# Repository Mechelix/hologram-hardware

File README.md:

# Hologram Dash and Dash Pro Hardware Repo

Welcome to Hologram
We hope you enjoy using our hardware

This is the repo for the Dash and Dash Pro

You can find everything you need to at
https://hologram.io/start

You can find the user manual here:
https://hologram.io/docs/hardware/hologram-dash/

There is also a great index of documentation here:
https://hologram.io/docs/

You can find our forums here. We really want to hear about your projects!
https://community.hologram.io/

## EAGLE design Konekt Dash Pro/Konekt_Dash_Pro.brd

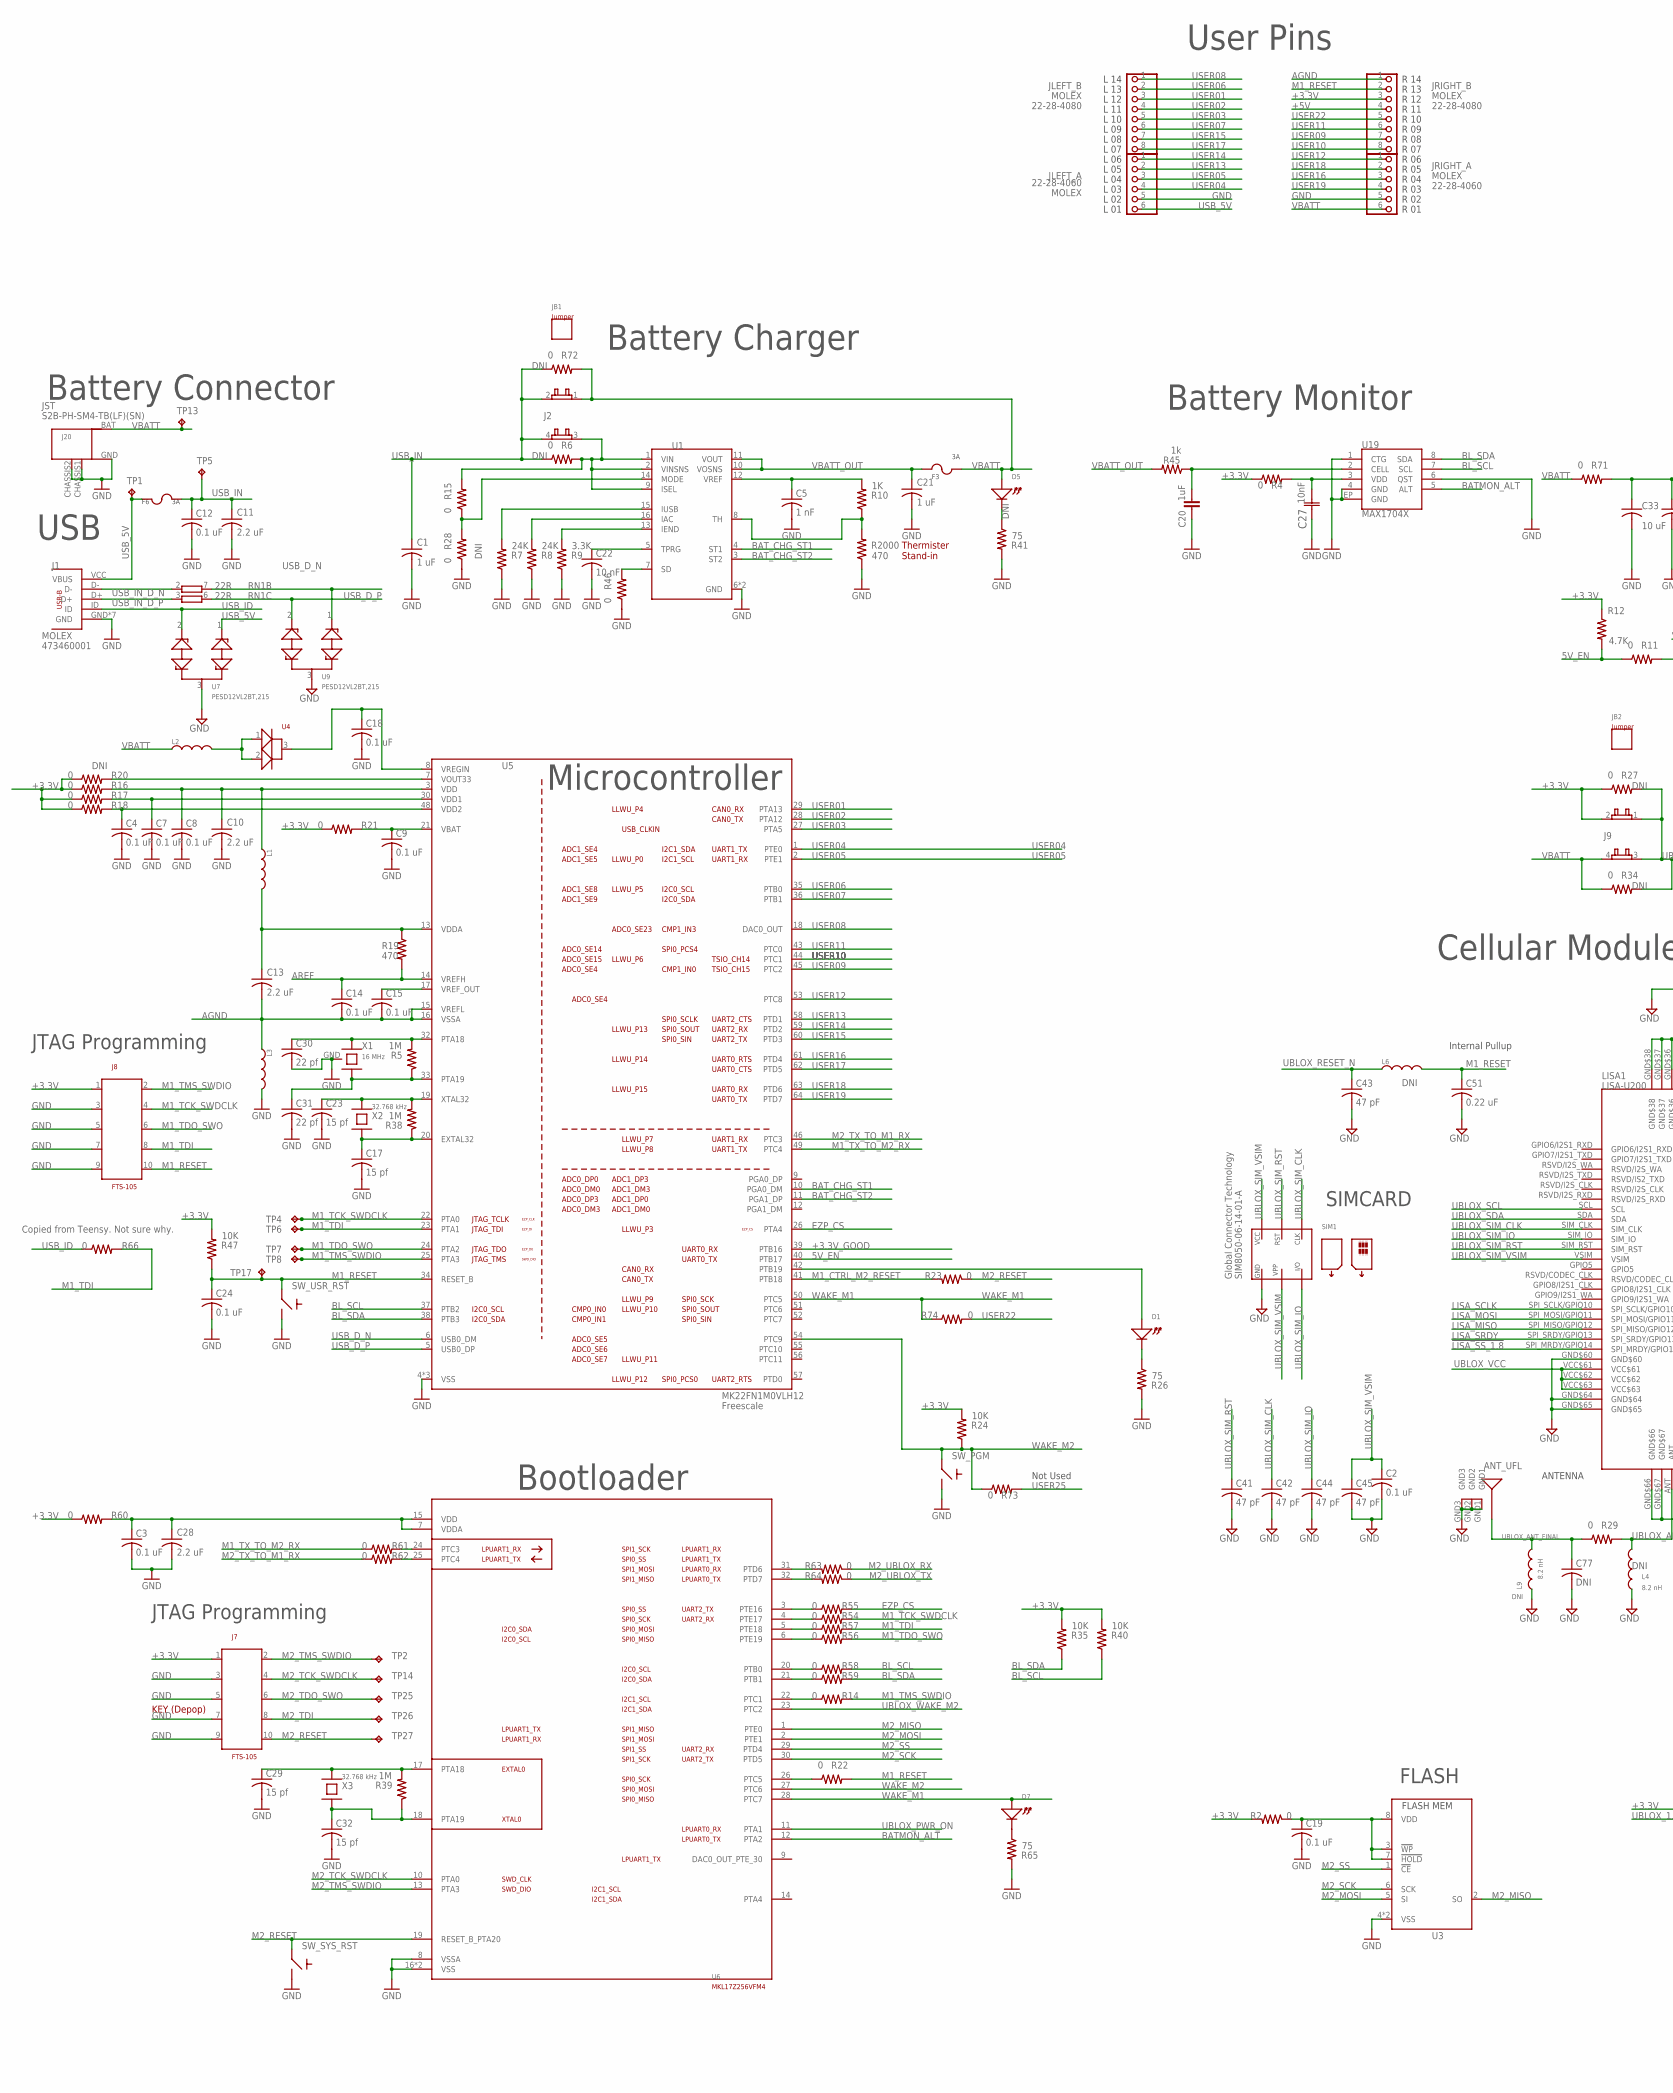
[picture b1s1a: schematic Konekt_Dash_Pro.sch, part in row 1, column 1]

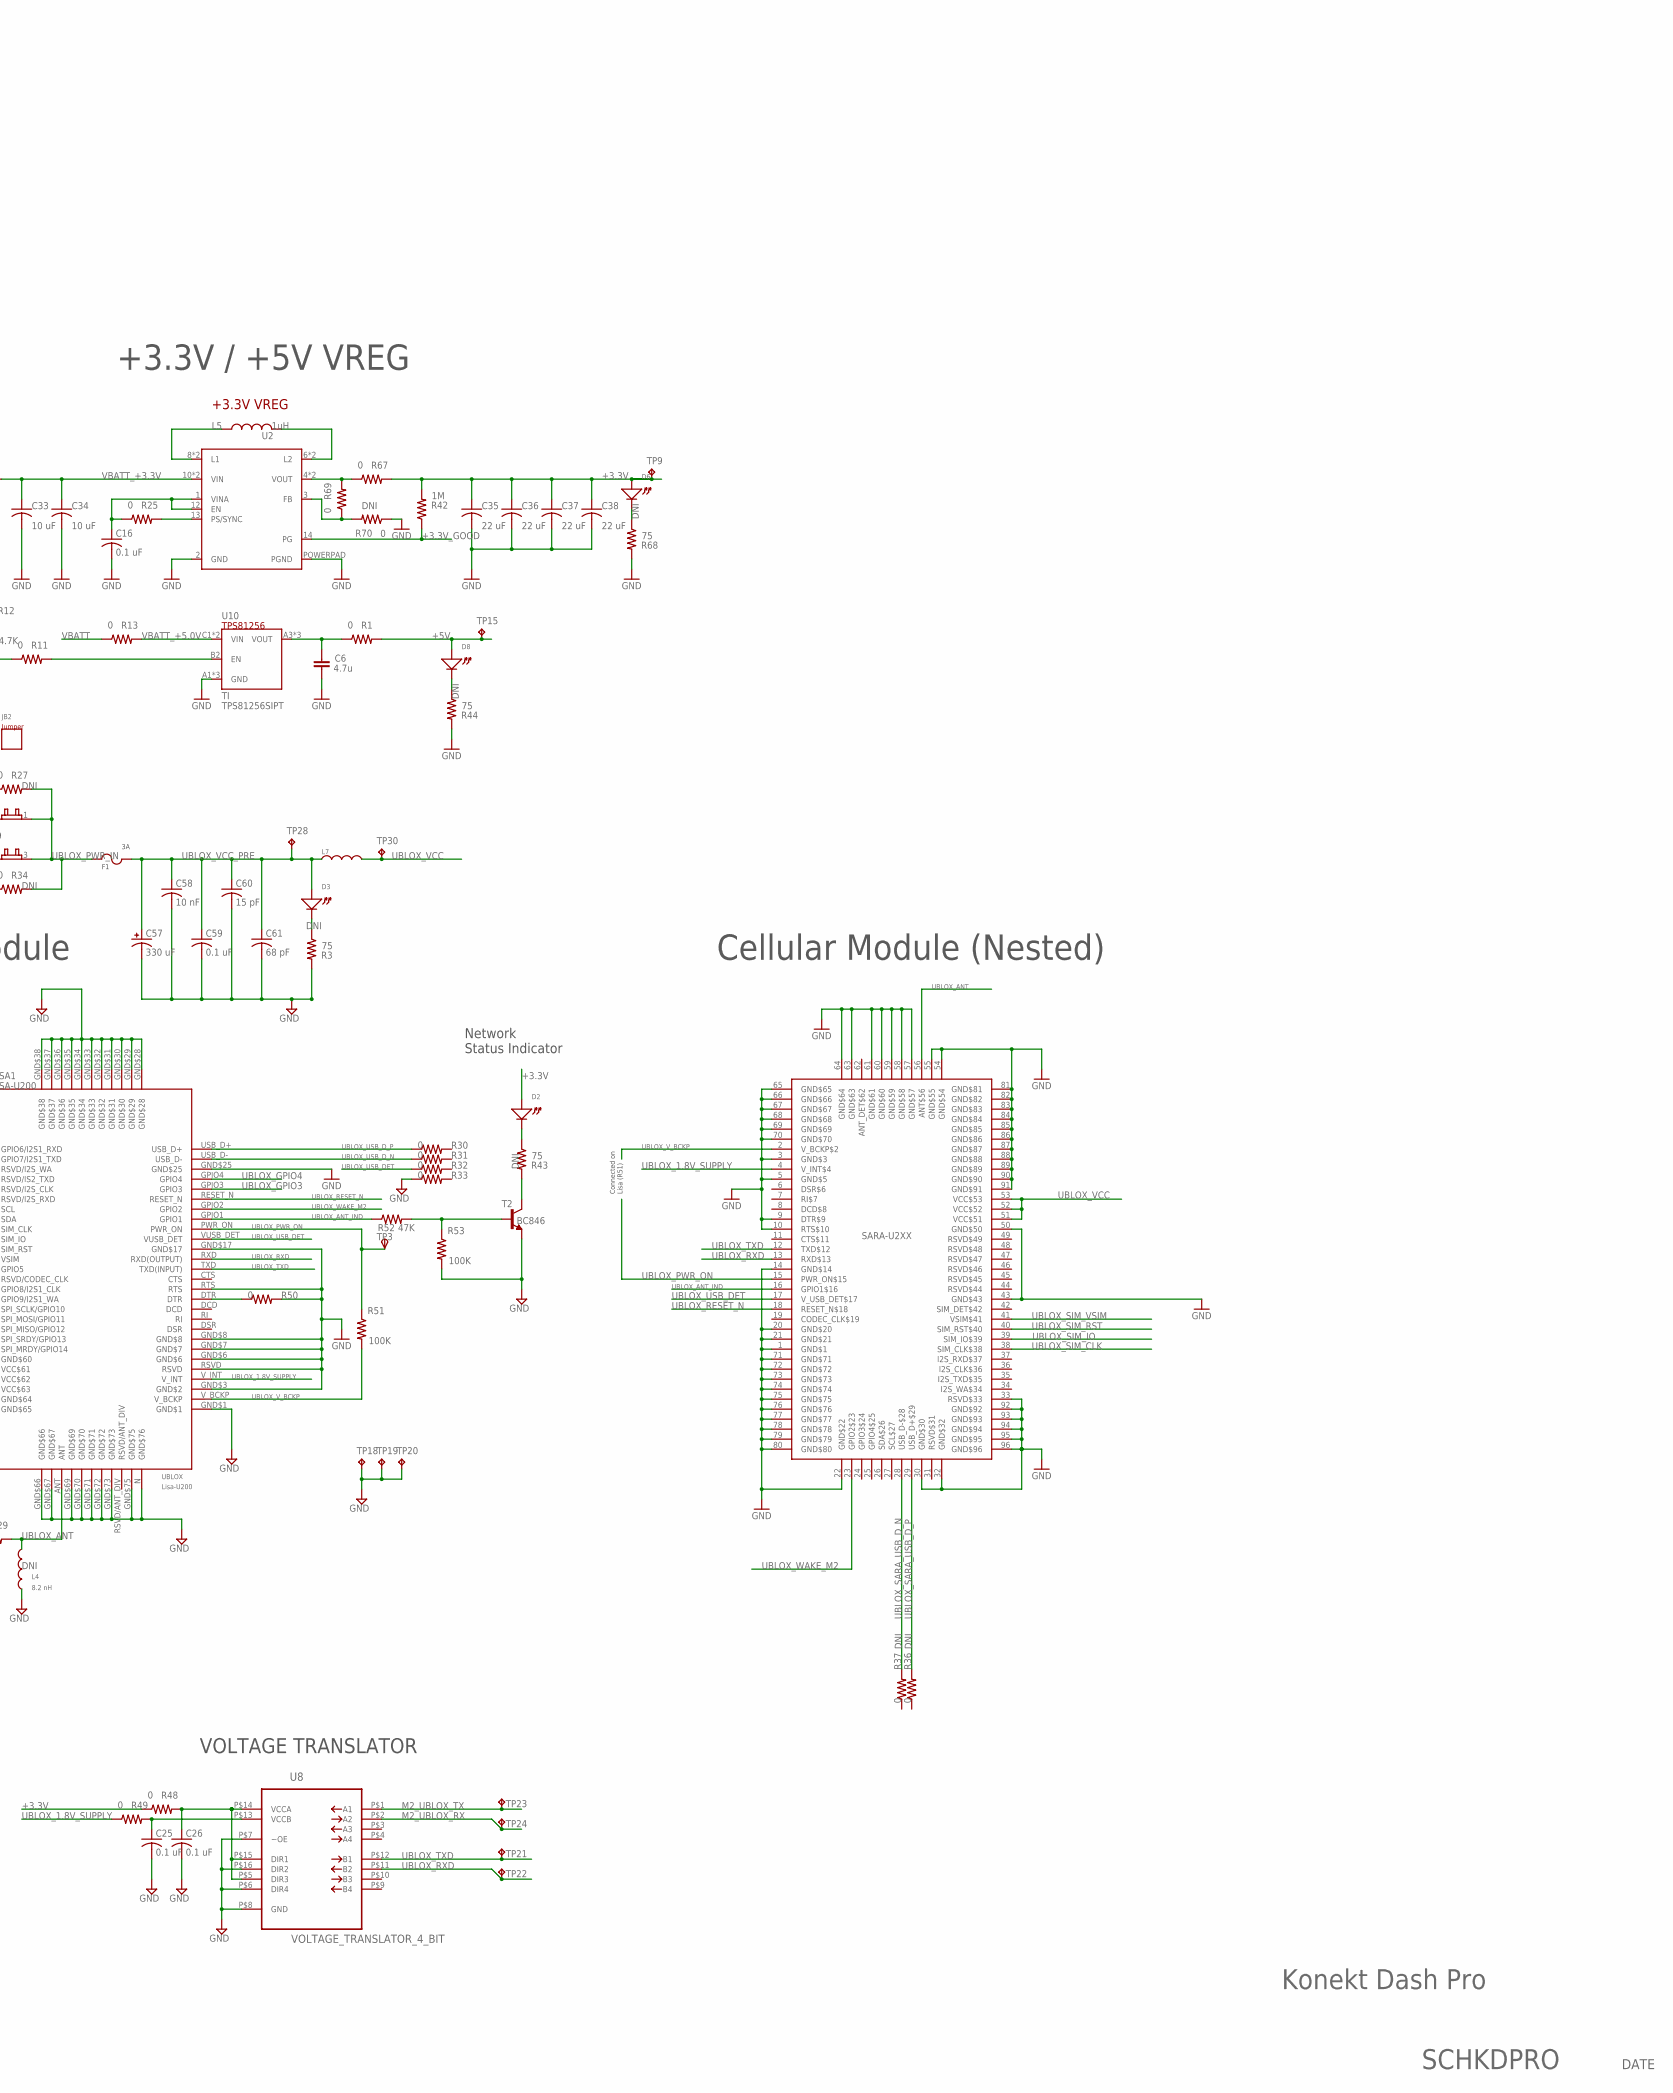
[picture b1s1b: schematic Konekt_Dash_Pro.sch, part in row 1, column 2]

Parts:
ANT_UFL: ANT-A-1JB; UFL; MPN A-1JB
C1, C21: 1 uF; C0603; MPN GRM188R71C105KA12D
C2, C3, C4, C7, C8, C9, C14, C15, C18, C19, C24, C25, C26: 0.1 uF; C0402; MPN GRM155R61C104KA88D
C5: 1 nF; C0402; MPN GRM319R71H102KA01D
C6: 4.7u; C0603-ROUND; MPN GRM188R61C475KAAJD
C10, C11, C13, C28: 2.2 uF; C0603; MPN CL10A225MQ8NNNC
C12, C16, C59: 0.1 uF; C0603; MPN 0603YC104KAT2A
C17, C23, C29, C32: 15 pf; C0402; MPN 04025A150JAT2A
C20: 1uF; 0402-CAP; TOLERANCE 10%; VOLTAGE 50V; MPN 04026D105KAT2A
C22, C58: 10 nF; C0402; MPN GRM155R71C103KA01D
C27: 10nF; CAPC1005X60N
C30, C31: 22 pf; C0402; MPN 04025A220JAT2A
C33, C34: 10 uF; C0603; MPN GRM188R60J106ME84D
C35, C36, C37, C38: 22 uF; C0603; MPN GRM188R60J226MEA0D
C41, C42, C43, C44, C45: 47 pF; C0402; MPN 04025A470JAT2A
C51: 0.22 uF; C0603; MPN 0603YC224KAT2A
C57: 330 uF; CAP_SMD_SIZE_D; MPN T520D337M006ATE045
C60: 15 pF; C0402; MPN NMC0402NPO150J50TRPF
C61: 68 pF; C0402; MPN GRM1555C1H680JA01D
C77: DNI; C0402; MPN DNI
D1, D2, D3, D5, D6, D7, D8: LED_0402_VLMW; LED_0402_VISHAY_VLMW
F1, F3, F6: 3A; R0603; MPN SF-0603S300-2
J1: USB_MICRO_B_MOLEX_473460001; USB_MICRO_MOLEX_473460001; MPN 473460001
J2, J9: CON_JUMPER_1.27_2X2; FCI_CON_1.27_2X2
J7, J8: FTS-105; MPN FTS-105-01-F-DV
J20: BAT_TERM; JST-PH-2; MPN S2B-PH-SM4-TB(LF)(SN)
JB1, JB2: JUMPER_1.27MM; NOTHING
JLEFT_A: PINHD-1X6; 1X06; MPN 22-28-4060
JLEFT_B: HEADER_0.1_IN_8_POS; HEADER_0.1_8_POS; MPN 22-28-4080
JRIGHT_A: PINHD-1X6; 1X06; MPN 22-28-4060
JRIGHT_B: HEADER_0.1_IN_8_POS; HEADER_0.1_8_POS; MPN 22-28-4080
L1, L3: INDUCTOR_0603; R0603$1; MPN BLM18AG121SN1D
L2: INDUCTOR_0603; R0603$1; MPN MPZ1608S221A
L4, L9: INDUCTOR_0402; R0402; MPN DNI
L5: 1uH; COILCRAFT_XFL4020
L6: INDUCTOR_0603; R0603$1; MPN DNI
L7: INDUCTOR_0603; R0603$1; MPN BLM18EG221SN1D
LISA1: LISA-U200; 76PIN_LCC; MPN LISA-U200-02S
R1, R2, R4, R11, R13, R14, R15, R16, R17, R18, R21, R22, R23, R25, R29, R30, R31, R32, R33, R46, R48, R49, R50, R54, R55, R56, R57, R58, R59, R60, R61, R62, R63, R64, R66, R67, R69, R71, R73, R74: 0; 0402-RES; MPN ERJ-2GE0R00X
R3, R41, R43, R44, R68: 75; 0402-RES; MPN DNI
R5, R38, R39, R42: 1M; 0402-RES; MPN RC0402JR-071ML
R6, R20, R27, R28, R34, R36, R37, R70, R72: 0; 0402-RES; MPN DNI
R7, R8: 24K; 0402-RES; MPN RC0402JR-0724KL
R9: 3.3K; 0402-RES; MPN RC0402JR-073K3L
R10: 1K; 0402-RES; MPN RC0402JR-071KL
R12: 4.7K; R0402; MPN ERJ-2GEJ472X
R19: 470; R0402; MPN ERJ-2GEJ471X
R24, R35, R40, R47: 10K; 0402-RES; MPN RC0402JR-0710KL
R26, R65: 75; 0402-RES; MPN ERJ-2GEJ750X
R45: 1k; 0402-RES; TOLERANCE 5%; MPN RC0402JR-071KL
R51, R53: 100K; R0402; MPN ERJ-2GEJ104X
R52: 47K; R0402; MPN ERJ-2GEJ473X
R2000: 470; 0402-RES; MPN RC0402JR-07470RL
RN1: 22R; CAY16; MPN CAY16-220J4LF
SARA1: SARA-U2XX; 91-PIN_LGA; MPN DNI
SIM1: SIM_CARD_NANO_GLOBAL_CONNECTOR_TEC_SIM8050-6-0-14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; SIM_CARD_NANO
SW_PGM: SWITCH_PANASONIC_EVP-BB2A1B000; SWITCH_PANASONIC_EVPBB
SW_SYS_RST: SWITCH_PANASONIC_EVP-BB2A1B000; SWITCH_PANASONIC_EVPBB
SW_USR_RST: SWITCH_PANASONIC_EVP-BB2A1B000; SWITCH_PANASONIC_EVPBB
T2: BC846; SOT23; MPN BC846ALT1G
TP1, TP2, TP4, TP5, TP6, TP7, TP8, TP9, TP13, TP14, TP15, TP17, TP18, TP19, TP20, TP21, TP22, TP23, TP24, TP25, TP26, TP27, TP28, TP30: TPTP08R; TP08R; MPN N/A
TP3: TPSTP09R; TP09R; MPN N/A
U1: ST_MICRO_BAT_CHARGER_L6924U013; BAT_CHARGE_ST_MICRO_L6924U; MPN L6924UTR
U2: TPS63021; QFN-14-POWERPAD3X4DSJ; MPN TPS63021DSJR
U3: MICROCHIP_FLASH_MEM; TDFN8_5X6; MPN SST26VF016BT-104I/MF
U4: DIODE_DUAL_SCHOTKEY; SOT23-3; MPN_DNI BAT54C
U5: MK20DX128VLH5; MPN MK22FN1M0VLH12
U6: FREESCALE_MKL17Z256VFM4; QFN_32_5X5
U7, U9: PESD12VL2BT,215; SOT23; MPN PESD12VL2BT,215
U8: VOLTAGE_TRANSLATOR_4_BIT; UQFN_16
U10: BOOST_5V_TI_TPS81256; MICRO_SIP_3X3
U19: MAX1704X; TDFN-8; MPN MAX17043G+U
X1: 16 MHz; CRYSTAL_RESONATOR_MURATA_CSTCE
X2, X3: 32.768 kHz; CRYSTAL_ST3215SB

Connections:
5V_EN: R11.1, R12.2, U5.40 (PTB17)
!LISA_SS_1.8: LISA1.SPI_MRDY/GPIO14
+3.3V: C35.1, C36.1, C37.1, C38.1, D2.ANODE, D6.ANODE, J7.1, J8.1, J9.2, JRIGHT_B.3, R2.2, R4.1, R12.1, R16.1, R17.1, R18.1, R20.1, R21.1, R24.2, R27.1, R35.2, R40.2, R42.2, R47.2, R48.1, R60.1, R67.2, TP9.TP
+3.3V_FLASH: C19.1, R2.1, U3.3 (!WP), U3.7 (!HOLD), U3.8 (VDD)
+3.3V_GOOD: R42.1, U2.14 (PG), U5.39 (PTB16)
+5V: D8.ANODE, JRIGHT_B.4, R1.2, TP15.TP
AGND: C13.2, C14.2, C15.2, JRIGHT_B.1, L3.1, U5.15 (VREFL), U5.16 (VSSA)
ANT_DET$62: SARA1.62 (ANT_DET$62)
AREF: C14.1, R19.2, U5.14 (VREFH)
BATMON_ALT: U6.12 (PTA2), U19.5 (ALT)
BAT_CHG_ST1: U1.4 (ST1), U5.10 (PGA0_DM)
BAT_CHG_ST2: U1.3 (ST2), U5.11 (PGA1_DP)
BL_SCL: R40.1, R58.2, U5.37 (PTB2), U19.7 (SCL)
BL_SDA: R35.1, R59.2, U5.38 (PTB3), U19.8 (SDA)
EZP_CS: R55.2, U5.26 (PTA4)
GND: ANT_UFL.GND1, ANT_UFL.GND2, ANT_UFL.GND3, C1.2, C2.2, C3.2, C4.2, C5.2, C6.1, C7.2, C8.2, C9.2, C10.2, C11.2, C12.2, C16.2, C17.2, C18.2, C19.2, C20.2, C21.2, C22.2, C23.2, C24.2, C25.2, C26.2, C27.1 (C1), C28.2, C29.2, C30.2, C31.2, C32.2, C33.2, C34.2, C35.2, C36.2, C37.2, C38.2, C41.2, C42.2, C43.2, C44.2, C45.2, C51.2, C57.P$2 (NEG), C58.2, C59.2, C60.2, C61.2, C77.2, J1.GND, J1.GND$1 (GND), J1.GND$2 (GND), J1.GND$3 (GND), J1.GND$4 (GND), J1.GND$5 (GND), J1.GND$6 (GND), J7.3, J7.5, J7.7, J7.9, J8.3, J8.5, J8.7, J8.9, J20.CHASSIS1 (CHASSIS_1), J20.CHASSIS2 (CHASSIS_2), J20.GND, JLEFT_A.5, JRIGHT_A.5, L3.2, L4.2, L9.2, LISA1.GND$1, LISA1.GND$3 (GND$2), LISA1.GND$6, LISA1.GND$7, LISA1.GND$8, LISA1.GND$17, LISA1.GND$25, LISA1.GND$28, LISA1.GND$29, LISA1.GND$30, LISA1.GND$31, LISA1.GND$32, LISA1.GND$33, LISA1.GND$34, LISA1.GND$35, LISA1.GND$36, LISA1.GND$37, LISA1.GND$38, LISA1.GND$60, LISA1.GND$64, LISA1.GND$65, LISA1.GND$66, LISA1.GND$67, LISA1.GND$69, LISA1.GND$70, LISA1.GND$71, LISA1.GND$72, LISA1.GND$73, LISA1.GND$75, LISA1.N (GND$76), LISA1.RSVD, LISA1.RTS, R3.2, R7.1, R8.1, R9.1, R26.2, R28.1, R33.1, R41.2, R44.2, R46.1, R50.2, R53.2, R65.2, R68.2, R70.1, R2000.1, SARA1.1 (GND$1), SARA1.3 (GND$3), SARA1.5 (GND$5), SARA1.9 (DTR$9), SARA1.10 (RTS$10), SARA1.14 (GND$14), SARA1.20 (GND$20), SARA1.21 (GND$21), SARA1.22 (GND$22), SARA1.30 (GND$30), SARA1.32 (GND$32), SARA1.33 (RSVD$33), SARA1.43 (GND$43), SARA1.50 (GND$50), SARA1.54 (GND$54), SARA1.55 (GND$55), SARA1.57 (GND$57), SARA1.58 (GND$58), SARA1.59 (GND$59), SARA1.60 (GND$60), SARA1.61 (GND$61), SARA1.63 (GND$63), SARA1.64 (GND$64), SARA1.65 (GND$65), SARA1.66 (GND$66), SARA1.67 (GND$67), SARA1.68 (GND$68), SARA1.69 (GND$69), SARA1.70 (GND$70), SARA1.71 (GND$71), SARA1.72 (GND$72), SARA1.73 (GND$73), SARA1.74 (GND$74), SARA1.75 (GND$75), SARA1.76 (GND$76), SARA1.77 (GND$77), SARA1.78 (GND$78), SARA1.79 (GND$79), SARA1.80 (GND$80), SARA1.81 (GND$81), SARA1.82 (GND$82), SARA1.83 (GND$83), SARA1.84 (GND$84), SARA1.85 (GND$85), SARA1.86 (GND$86), SARA1.87 (GND$87), SARA1.88 (GND$88), SARA1.89 (GND$89), SARA1.90 (GND$90), SARA1.91 (GND$91), SARA1.92 (GND$92), SARA1.93 (GND$93), SARA1.94 (GND$94), SARA1.95 (GND$95), SARA1.96 (GND$96), SIM1.C5-GND (GND), SW_PGM.B, SW_PGM.B2, SW_SYS_RST.B, SW_SYS_RST.B2, SW_USR_RST.B, SW_USR_RST.B2, T2.2 (E), TP18.TP, TP19.TP, TP20.TP, U1.6 (GND), U1.PAD (GND), U2.2 (GND), U2.POWERPAD (PGND), U3.4 (VSS), U3.P$9 (VSS), U5.4 (VSS), U5.31 (VSS), U5.47 (VSS), U6.8 (VSSA), U6.16 (VSS), U6.PAD (VSS), U7.3, U8.P$6 (DIR4), U8.P$7 (~OE), U8.P$8 (GND), U8.P$16 (DIR2), U9.3, U10.A1 (GND), U10.A2 (GND), U10.B1 (GND), U19.1 (CTG), U19.4 (GND), U19.6 (QST), U19.EP (GND), X1.GND
GPIO4$25: SARA1.25 (GPIO4$25)
I2S_TXD$35: SARA1.35 (I2S_TXD$35)
I2S_WA$34: SARA1.34 (I2S_WA$34)
LISA_MISO: LISA1.SPI_MISO/GPIO12
LISA_MOSI: LISA1.SPI_MOSI/GPIO11
LISA_SCLK: LISA1.SPI_SCLK/GPIO10
LISA_SRDY: LISA1.SPI_SRDY/GPIO13
M1_CTRL_M2_RESET: R23.2, U5.41 (PTB18)
M1_RESET: C24.1, C51.1, J8.10, JRIGHT_B.2, L6.2, R22.2, R47.1, SW_USR_RST.A, SW_USR_RST.A2, TP17.TP, U5.34 (RESET_B)
M1_TCK_SWDCLK: J8.4, R54.2, TP4.TP, U5.22 (PTA0)
M1_TDI: J8.8, R57.2, R66.2, TP6.TP, U5.23 (PTA1)
M1_TDO_SWO: J8.6, R56.2, TP7.TP, U5.24 (PTA2)
M1_TMS_SWDIO: J8.2, R14.2, TP8.TP, U5.25 (PTA3)
M1_TX_TO_M2_RX: R61.1, U5.49 (PTC4)
M2_MISO: U3.2 (SO), U6.1 (PTE0)
M2_MOSI: U3.5 (SI), U6.2 (PTE1)
M2_RESET: J7.10, R23.1, SW_SYS_RST.A, SW_SYS_RST.A2, TP27.TP, U6.19 (RESET_B_PTA20)
M2_RX: R61.2, U6.24 (PTC3)
M2_SCK: U3.6 (SCK), U6.30 (PTD5)
M2_SPI0_MISO: R56.1, U6.6 (PTE19)
M2_SPI0_MOSI: R57.1, U6.5 (PTE18)
M2_SS: U3.1 (!CE), U6.29 (PTD4)
M2_TCK_SWDCLK: J7.4, TP14.TP, U6.10 (PTA0)
M2_TDI: J7.8, TP26.TP
M2_TDO_SWO: J7.6, TP25.TP
M2_TMS_SWDIO: J7.2, TP2.TP, U6.13 (PTA3)
M2_TX: R62.2, U6.25 (PTC4)
M2_TX_TO_M1_RX: R62.1, U5.46 (PTC3)
M2_UBLOX_RX: R63.1, TP24.TP, U8.P$2 (A2)
M2_UBLOX_TX: R64.1, TP23.TP, U8.P$1 (A1)
unnamed: C20.1, R45.1, U19.2 (CELL)
unnamed: D1.ANODE, U5.42 (PTB19)
unnamed: C27.2 (C2), R4.2, U19.3 (VDD)
unnamed: J2.3, R6.2, R15.2, U1.1 (VIN), U1.2 (VINSNS), U1.9 (ISEL)
unnamed: R10.1, R2000.2, U1.8 (TH)
unnamed: C5.1, R10.2, U1.12 (VREF)
unnamed: D3.CATHODE, R3.1
unnamed: R7.2, U1.15 (IUSB)
unnamed: L5.P$1, U2.8 (L1), U2.9 (L1)
unnamed: R8.2, U1.16 (IAC)
unnamed: C30.1, R5.2, U5.32 (PTA18), X1.XTAL1
unnamed: R9.2, U1.13 (IEND)
unnamed: D5.CATHODE, R41.1
unnamed: C22.1, U1.5 (TPRG)
unnamed: C6.2, R1.1, U10.A3 (VOUT), U10.B3 (VOUT), U10.C3 (VOUT)
unnamed: R11.2, U10.B2 (EN)
unnamed: C8.1, C10.1, L1.1, R16.2, U5.3 (VDD)
unnamed: C7.1, R17.2, U5.30 (VDD1)
unnamed: C4.1, R18.2, U5.48 (VDD2)
unnamed: C18.1, U4.3 (C), U5.8 (VREGIN)
unnamed: R20.2, U5.7 (VOUT33)
unnamed: C15.1, U5.17 (VREF_OUT)
unnamed: C13.1, L1.2, R19.1, U5.13 (VDDA)
unnamed: D8.CATHODE, R44.1
unnamed: L2.2, U4.1 (A1), U4.2 (A2)
unnamed: LISA1.DTR, R50.1
unnamed: C9.1, R21.2, U5.21 (VBAT)
unnamed: C31.1, R5.1, U5.33 (PTA19), X1.XTAL2
unnamed: C23.1, R38.2, U5.19 (XTAL32), X2.P$2 (XTAL2)
unnamed: R58.1, U6.20 (PTB0)
unnamed: C17.1, R38.1, U5.20 (EXTAL32), X2.P$1 (XTAL1)
unnamed: L5.P$2, U2.6 (L2), U2.7 (L2)
unnamed: D1.CATHODE, R26.1
unnamed: C16.1, R25.1, U2.1 (VINA), U2.12 (EN)
unnamed: R14.1, U6.22 (PTC1)
unnamed: R15.1, R28.2, U1.14 (MODE)
unnamed: R46.2, U1.7 (SD)
unnamed: R67.1, R69.2, U2.4 (VOUT), U2.5 (VOUT)
unnamed: R63.2, U6.31 (PTD6)
unnamed: R64.2, U6.32 (PTD7)
unnamed: R55.1, U6.3 (PTE16)
unnamed: R54.1, U6.4 (PTE17)
unnamed: R59.1, U6.21 (PTB1)
unnamed: R22.1, U6.26 (PTC5)
unnamed: C3.1, C28.1, R60.2, U6.7 (VDDA), U6.15 (VDD)
unnamed: D7.CATHODE, R65.1
unnamed: C32.1, R39.1, U6.18 (PTA19), X3.P$1 (XTAL1)
unnamed: C29.1, R39.2, U6.17 (PTA18), X3.P$2 (XTAL2)
unnamed: R25.2, U2.13 (PS/SYNC)
unnamed: D6.CATHODE, R68.1
unnamed: R69.1, R70.2, U2.3 (FB)
unnamed: D2.CATHODE, R43.1
unnamed: R52.2, R53.1, T2.1 (B)
unnamed: R43.2, T2.3 (C)
RSVD$31: SARA1.31 (RSVD$31)
SCL$27: SARA1.27 (SCL$27)
SDA$26: SARA1.26 (SDA$26)
UBLOX_1.8V_SUPPLY: LISA1.V_INT, R49.1, SARA1.4 (V_INT$4)
UBLOX_ANT: L4.1, LISA1.ANT, R29.2, SARA1.56 (ANT$56)
UBLOX_ANT_FINAL: ANT_UFL.SIGNAL, C77.1, L9.1, R29.1
UBLOX_ANT_IND: LISA1.GPIO1, R52.1, SARA1.16 (GPIO1$16)
UBLOX_GPIO3: LISA1.GPIO3
UBLOX_GPIO4: LISA1.GPIO4
UBLOX_PWR_IN: F1.2, J9.1, J9.3, R27.2, R34.2
UBLOX_PWR_ON: LISA1.PWR_ON, R51.1, SARA1.15 (PWR_ON$15), TP3.TP, U6.11 (PTA1)
UBLOX_RESET_N: C43.1, L6.1, LISA1.RESET_N, SARA1.18 (RESET_N$18)
UBLOX_RXD: LISA1.RXD (RXD(OUTPUT)), SARA1.13 (RXD$13), TP22.TP, U8.P$11 (B2)
UBLOX_SARA_USB_D_N: R37.2, SARA1.28 (USB_D-$28)
UBLOX_SARA_USB_D_P: R36.2, SARA1.29 (USB_D+$29)
UBLOX_SCL: LISA1.SCL
UBLOX_SDA: LISA1.SDA
UBLOX_SIM_CLK: C42.1, LISA1.SIM_CLK, SARA1.38 (SIM_CLK$38), SIM1.C3-CLK (CLK)
UBLOX_SIM_IO: C44.1, LISA1.SIM_IO, SARA1.39 (SIM_IO$39), SIM1.C7-IO (IO)
UBLOX_SIM_RST: C41.1, LISA1.SIM_RST, SARA1.40 (SIM_RST$40), SIM1.C2-RST (RST)
UBLOX_SIM_VSIM: C2.1, C45.1, LISA1.VSIM, SARA1.41 (VSIM$41), SIM1.C1-VCC (VCC), SIM1.C6-VPP (VCC2)
UBLOX_TXD: LISA1.TXD (TXD(INPUT)), SARA1.12 (TXD$12), TP21.TP, U8.P$12 (B1)
UBLOX_USB_DET: LISA1.VUSB_DET, R32.1, SARA1.17 (V_USB_DET$17)
UBLOX_USB_D_N: LISA1.USB_D-, R31.1
UBLOX_USB_D_P: LISA1.USB_D+, R30.1
UBLOX_VCC: L7.2, LISA1.VCC$61, LISA1.VCC$62, LISA1.VCC$63, SARA1.51 (VCC$51), SARA1.52 (VCC$52), SARA1.53 (VCC$53), TP30.TP
UBLOX_VCC_PRE: C57.P$1 (POS), C58.1, C59.1, C60.1, C61.1, D3.ANODE, F1.1, L7.1, TP28.TP
UBLOX_V_BCKP: LISA1.V_BCKP, R51.2, SARA1.2 (V_BCKP$2)
UBLOX_WAKE_M2: LISA1.GPIO2, SARA1.23 (GPIO2$23), U6.23 (PTC2)
USB_5V: F6.1, J1.VCC (VBUS), JLEFT_A.6, TP1.TP, U7.1
USB_D_N: RN1.7 (2), U5.6 (USB0_DM), U9.1
USB_D_P: RN1.6 (2), U5.5 (USB0_DP), U9.2
USB_ID: J1.ID, R66.1, U7.2
USB_IN: C1.1, C11.1, C12.1, F6.2, J2.2, J2.4, R6.1, R72.1, TP5.TP
USB_IN_D_N: J1.D-, RN1.2 (1)
USB_IN_D_P: J1.D+, RN1.3 (1)
USER01: JLEFT_B.3, U5.29 (PTA13)
USER02: JLEFT_B.4, U5.28 (PTA12)
USER03: JLEFT_B.5, U5.27 (PTA5)
USER04: JLEFT_A.4, U5.1 (PTE0)
USER05: JLEFT_A.3, U5.2 (PTE1)
USER06: JLEFT_B.2, U5.35 (PTB0)
USER07: JLEFT_B.6, U5.36 (PTB1)
USER08: JLEFT_B.1, U5.18 (DAC0_OUT)
USER09: JRIGHT_B.7, U5.45 (PTC2)
USER10: JRIGHT_B.8, U5.44 (PTC1)
USER11: JRIGHT_B.6, U5.43 (PTC0)
USER12: JRIGHT_A.1, U5.53 (PTC8)
USER13: JLEFT_A.2, U5.58 (PTD1)
USER14: JLEFT_A.1, U5.59 (PTD2)
USER15: JLEFT_B.7, U5.60 (PTD3)
USER16: JRIGHT_A.3, U5.61 (PTD4)
USER17: JLEFT_B.8, U5.62 (PTD5)
USER18: JRIGHT_A.2, U5.63 (PTD6)
USER19: JRIGHT_A.4, U5.64 (PTD7)
USER22: JRIGHT_B.5, R74.2
USER25: R73.2
VBATT: D5.ANODE, F3.1, J2.1, J9.4, J20.BAT, JRIGHT_A.6, L2.1, R13.1, R34.1, R71.1, R72.2, TP13.TP
VBATT_+3.3V: C33.1, C34.1, R71.2, U2.10 (VIN), U2.11 (VIN)
VBATT_+5.0V: R13.2, U10.C1 (VIN), U10.C2 (VIN)
VBATT_OUT: C21.1, F3.2, R45.2, U1.10 (VOSNS), U1.11 (VOUT)
VTL_+3.3V1: C26.1, R48.2, U8.P$5 (DIR3), U8.P$14 (VCCA), U8.P$15 (DIR1)
VTL_LISA_VCC1: C25.1, R49.2, U8.P$13 (VCCB)
WAKE_M1: D7.ANODE, R74.1, U5.50 (PTC5), U6.28 (PTC7)
WAKE_M2: R24.1, R73.1, SW_PGM.A, SW_PGM.A2, U5.54 (PTC9), U6.27 (PTC6)

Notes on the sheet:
Network Status Indicator
SIMCARD
LISA1
Microcontroller
Thermister Stand-in
User Pins
Bootloader
Battery Connector
USB
Battery Charger
Battery Monitor
+3.3V / +5V VREG
ANTENNA
VOLTAGE TRANSLATOR
+3.3V VREG
EZP_CLK
EZP_DI
EZP_D0
SWD_DIO
EZP_CS
JTAG Programming
KEY (Depop)
Copied from Teensy. Not sure why.
Cellular Module (Nested)
Konekt Dash Pro
DATE
SCHKDPRO
Cellular Module
FLASH
Connected on Lisa (R51)
R 01
R 02
R 03
R 04
R 05
R 06
R 07
R 08
R 09
R 10

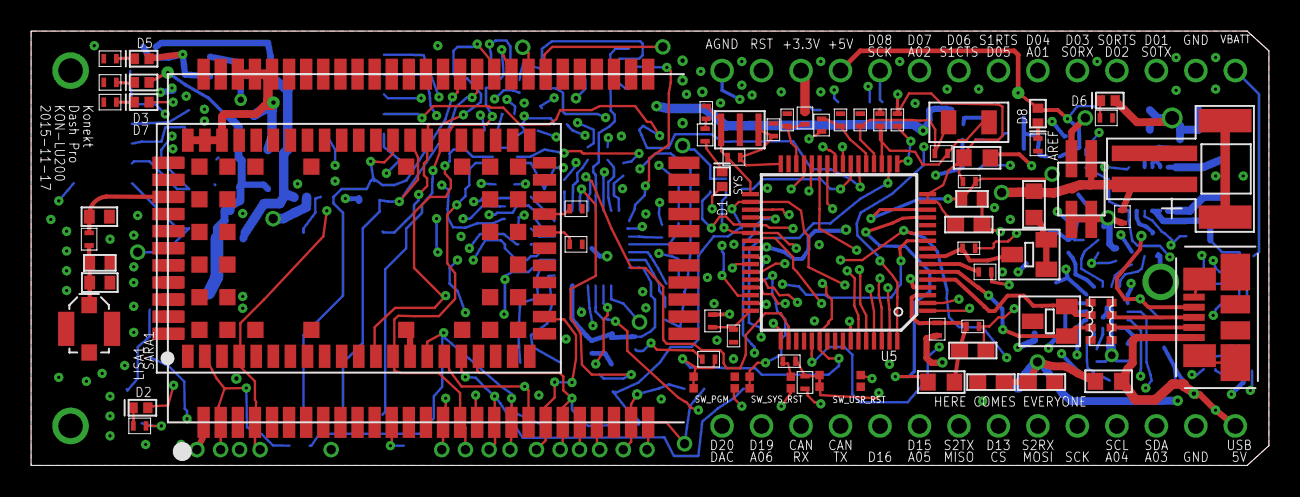
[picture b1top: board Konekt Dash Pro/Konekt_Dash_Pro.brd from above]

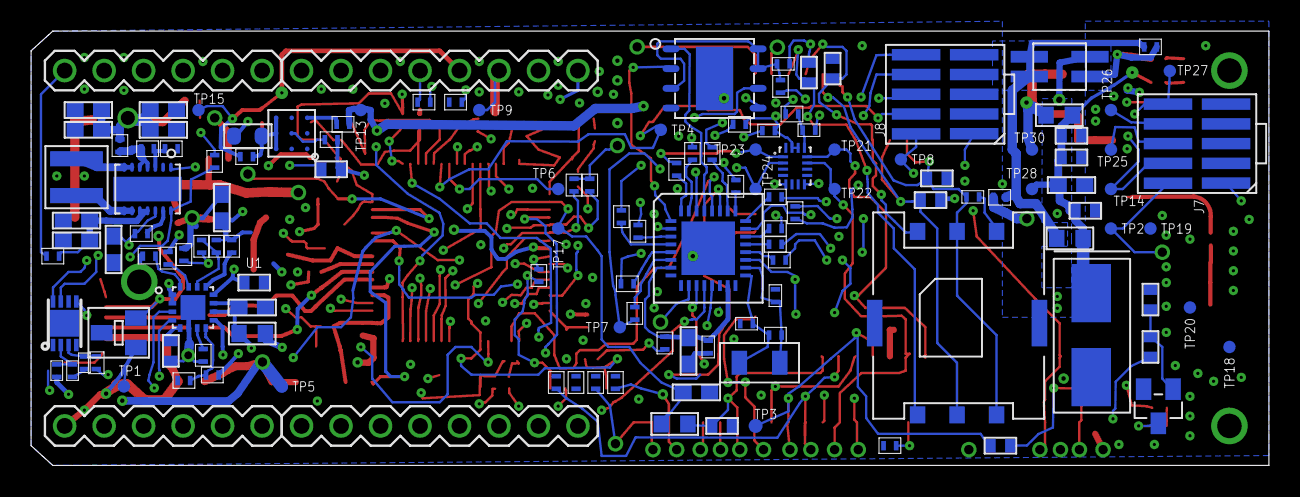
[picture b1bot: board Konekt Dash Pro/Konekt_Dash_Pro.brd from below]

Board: 6 copper layers, 79.6 x 27.9 mm, 203 parts (135 on the bottom side), 148 nets.

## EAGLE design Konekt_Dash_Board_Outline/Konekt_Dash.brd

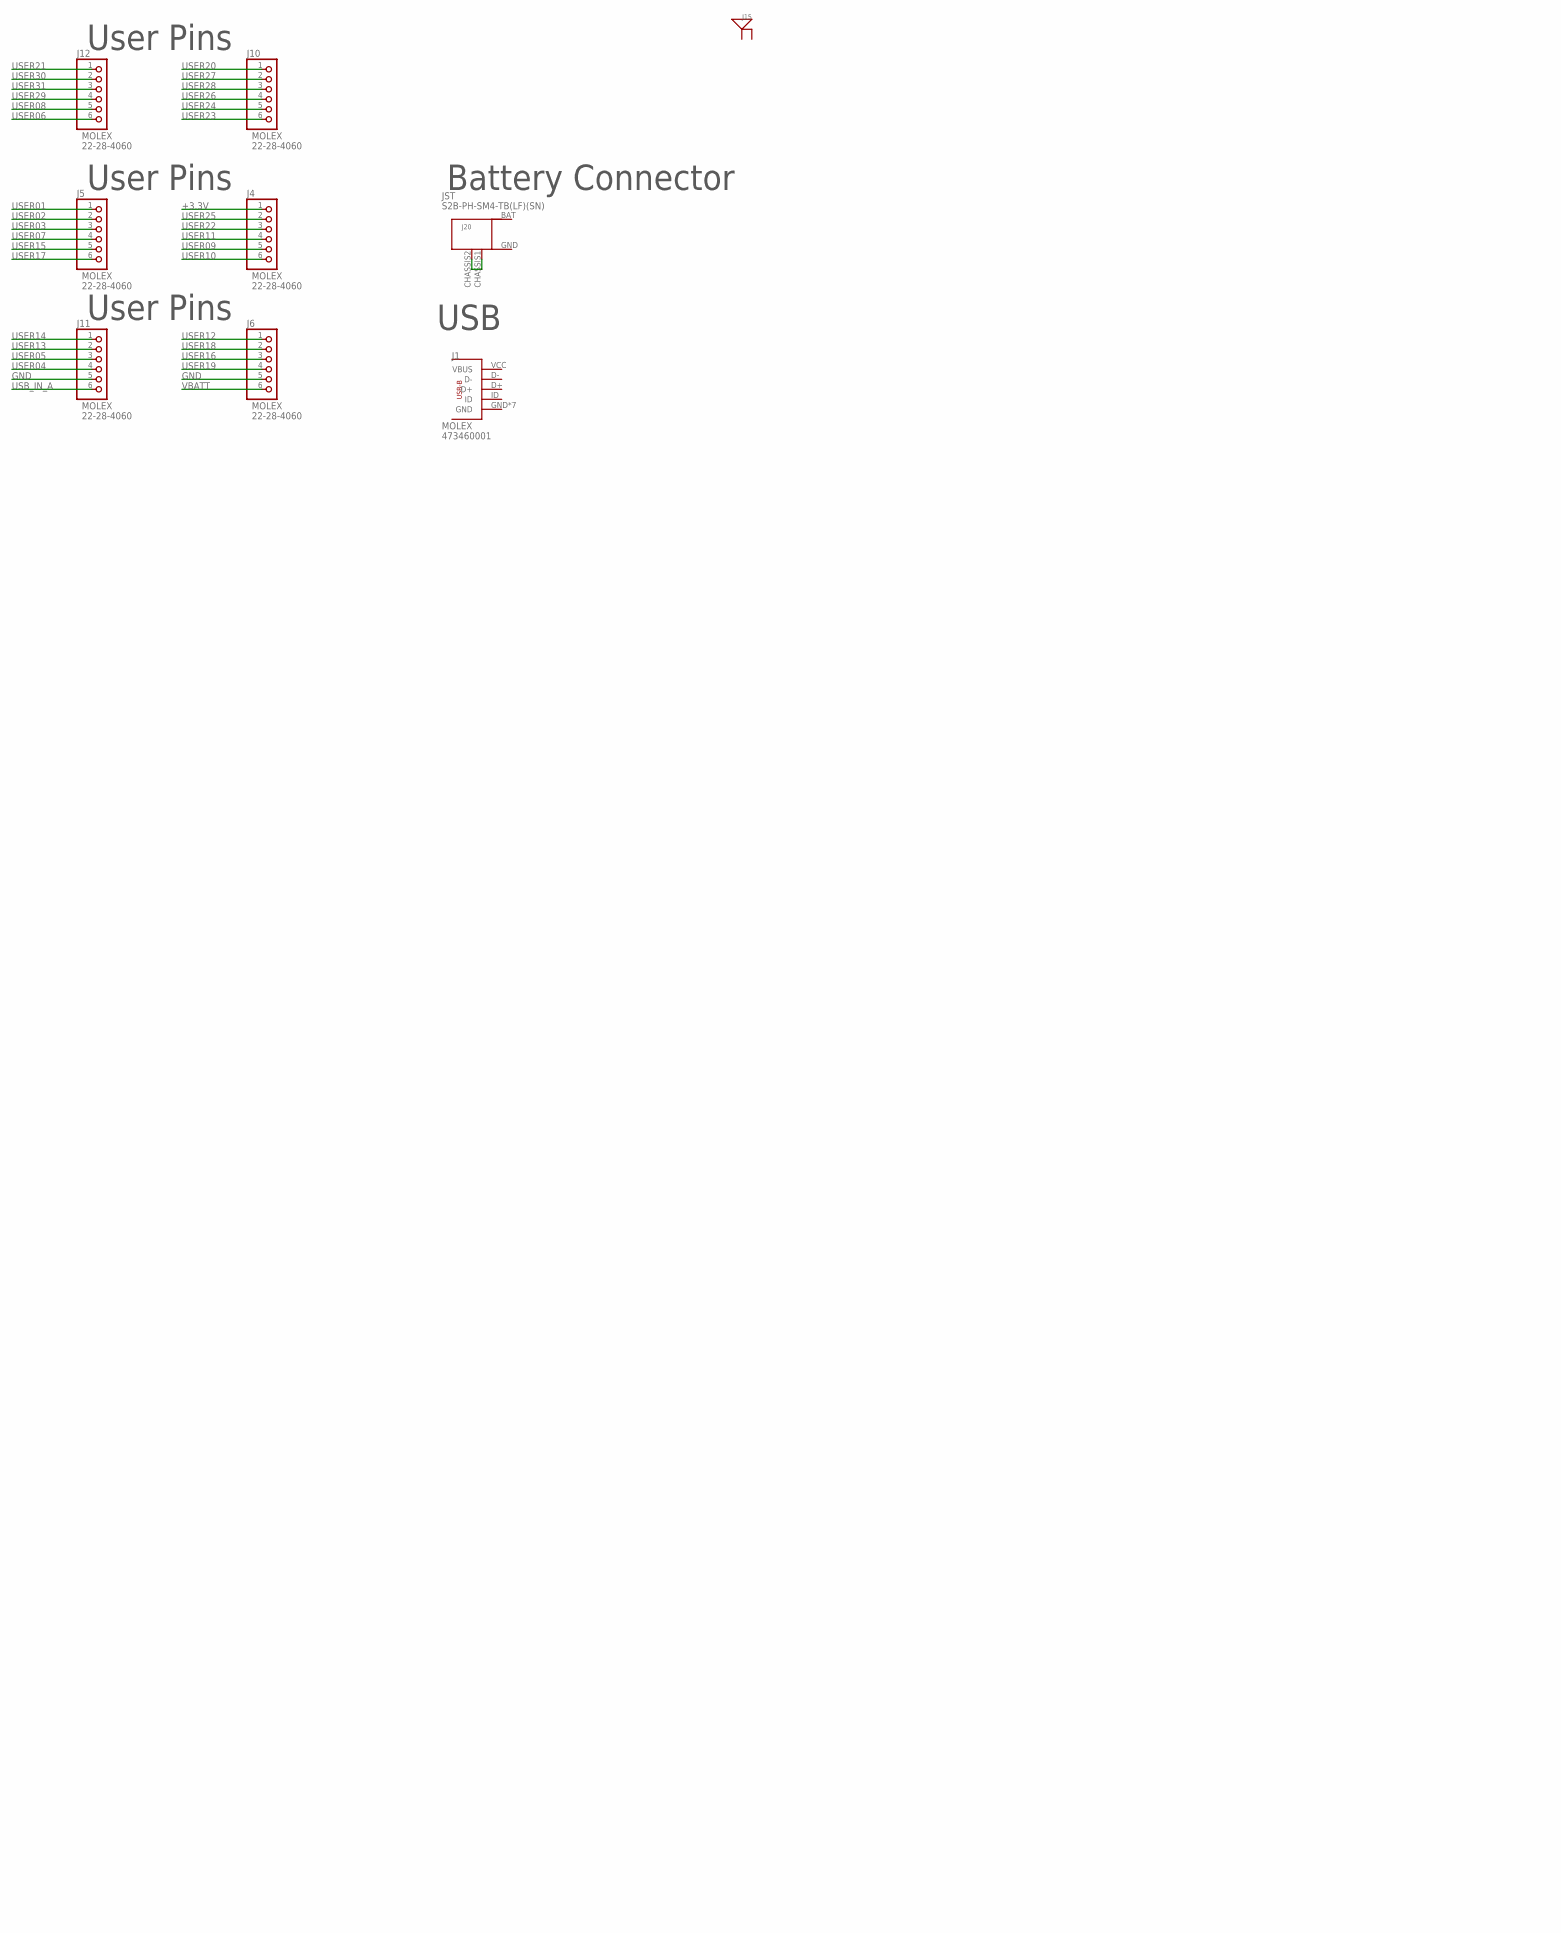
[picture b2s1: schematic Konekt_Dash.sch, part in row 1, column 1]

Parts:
J1: USB_MICRO_B_MOLEX_473460001; USB_MICRO_MOLEX_473460001; MPN 473460001
J4, J5, J6, J10, J11, J12: PINHD-1X6; 1X06; MPN 22-28-4060
J15: ANT_UFL; U.FL_CONNECTOR
J20: BAT_TERM; JST-PH-2; MPN S2B-PH-SM4-TB(LF)(SN)

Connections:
+3.3V: J4.1
GND: J6.5, J11.5
unnamed: J20.CHASSIS1 (CHASSIS_1), J20.CHASSIS2 (CHASSIS_2)
USB_IN_A: J11.6
USER01: J5.1
USER02: J5.2
USER03: J5.3
USER04: J11.4
USER05: J11.3
USER06: J12.6
USER07: J5.4
USER08: J12.5
USER09: J4.5
USER10: J4.6
USER11: J4.4
USER12: J6.1
USER13: J11.2
USER14: J11.1
USER15: J5.5
USER16: J6.3
USER17: J5.6
USER18: J6.2
USER19: J6.4
USER20: J10.1
USER21: J12.1
USER22: J4.3
USER23: J10.6
USER24: J10.5
USER25: J4.2
USER26: J10.4
USER27: J10.2
USER28: J10.3
USER29: J12.4
USER30: J12.2
USER31: J12.3
VBATT: J6.6

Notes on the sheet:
User Pins
Battery Connector
USB
Konekt Dash
SCHKD

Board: 8 copper layers, 9 parts (0 on the bottom side), 2 nets, no tracks yet.

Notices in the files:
Konekt Dash Pro/Konekt_Dash_Pro.brd:
Konekt Data, all rights reserved
parts and their libraries:
MAX1704: Licensing: CC v3.0 Share-Alike You are welcome to use this library for commercial purposes.
